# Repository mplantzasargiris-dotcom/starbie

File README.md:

# Starbie - Motion-Controlled Digital Pet

Starbie is a custom macropad PCB I designed for Half-lifes week 1.

I built this project to learn how to design a complete PCB, route connections, and place components properly in KiCad.

## Features:

* Custom routed PCB layout designed from scratch
* Fits mechanical key switches
* Built-in USB-C interface for power and data
* Compact macropad design

## What it is and why I made it:
Starbie is a custom-designed motion-controlled digital pet, built to function like a desktop Tamagotchi. I created this project to learn end-to-end PCB design, from drawing custom schematics and routing traces in KiCad to laying out physical components on a unique star-shaped board.

## How it works:
The board integrates a microcontroller (XIAO-ESP32-C3) connected to push buttons, indicator LEDs, and headers, allowing it to process user inputs and run digital pet logic.

## Schematics & Design:
Here is the schematic showing how all the components and power lines are wired together:

## PCB Design:

Everything was designed and routed in KiCad, focusing on clean trace routing and proper component layout for safe soldering and operation.

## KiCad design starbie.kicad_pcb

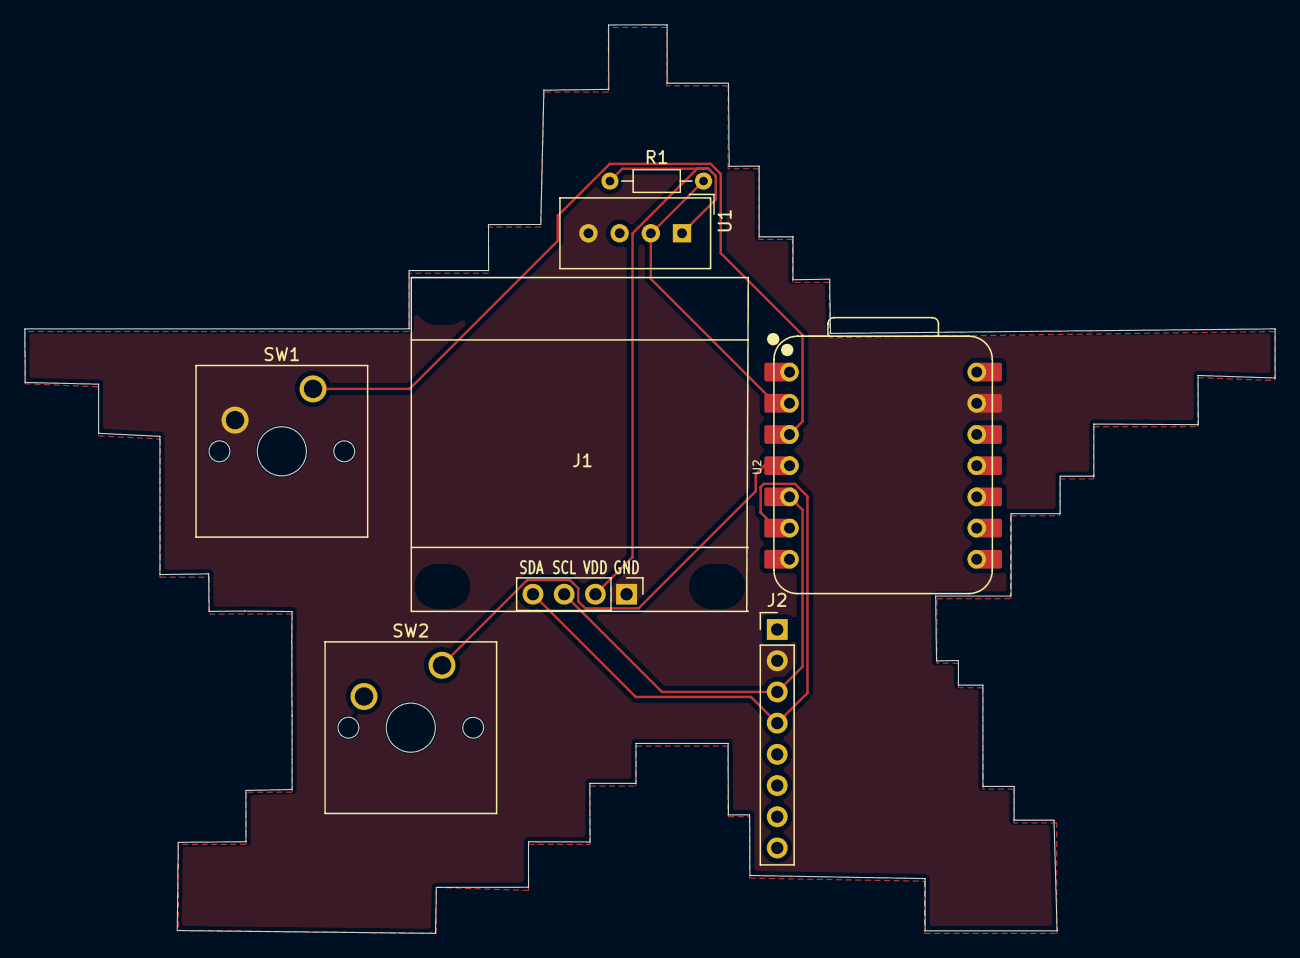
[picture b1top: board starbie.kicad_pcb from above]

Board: 2 copper layers, 101.8 x 74.0 mm, 7 parts (0 on the bottom side), 7 nets.

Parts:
J1: Conn_01x04_Pin; Display_128x64_096_I2C
J2: Conn_01x08_Pin; PinHeader_1x08_P2.54mm_Vertical
R1: 10k; R_Axial_DIN0204_L3.6mm_D1.6mm_P7.62mm_Horizontal
SW1, SW2: SW_Push; SW_Cherry_MX_1.00u_PCB
U1: DHT11; Aosong_DHT11_5.5x12.0_P2.54mm
U2: XIAO-ESP32-C3-SMD; XIAO-ESP32-C6-DIP

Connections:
+3.3V: J1.2, J2.1, R1.1, U1.1 (VDD), U2.12 (3V3_OUT)
/DHT11 DATA: R1.2, U1.2 (DATA), U2.2 (D1)
/GPIO2: SW1.1, U2.3 (D2)
/GPIO3: SW2.1 (1_1), U2.4 (D3)
/SCL: J1.3, J2.3, U2.5 (D4)
/SDA: J1.4, J2.4, U2.6 (D5)
GND: J1.1, J2.2, SW1.2, U1.4 (GND), U2.13 (GND)

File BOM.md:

# Starbie – bill of materials

<!-- Generated by Half Life from project cmuv88o5d0es601sm51l4azof. Edits here are overwritten on the next sync. -->
<!-- Generated: 2026-10-11T20:15:29.390Z -->

> [!NOTE]
> This parts list is mirrored from [Half Life](https://halflife.hackclub.com). Editing it here will not change the platform's copy, and the next sync overwrites this file.

| Week | Tier | Parts funding |
| --- | --- | --- |
| Week 1 | Tier 1 | $30.00 |

| Part | What it's for | Qty | Unit | Total | Vendor |
| --- | --- | --- | --- | --- | --- |
| [Conn_01x04_Pin](https://www.aliexpress.com/item/1005007093958549.html?spm=a2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 | Female header for expansions/l2C connections | 1 | $2.72 | $2.72 | [AliExpress](https://www.aliexpress.com/item/1005007093958549.html?spm=a2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 |
| [Conn_01x08_Pin](https://www.aliexpress.com/item/1005007093958549.html?spm=a2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 | 8-pin header for breakout connections or pin access. | 1 | $2.86 | $2.86 | [AliExpress](https://www.aliexpress.com/item/1005007093958549.html?spm=a2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 |
| [10k](https://www.aliexpress.com/item/1005010536514052.html?spm=a2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 | Pull-up resistor for button or data signal lines. | 1 | $0.78 | $0.78 | [AliExpress](https://www.aliexpress.com/item/1005010536514052.html?spm=a2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 |
| [SW_Push](https://www.aliexpress.com/item/32873398324.html?spm=a2g0o.c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 | buttons | 1 | $2.98 | $2.98 | [AliExpress](https://www.aliexpress.com/item/32873398324.html?spm=a2g0o.c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 |
| [DHT11](https://www.aliexpress.com/item/1005008953430940.html?spm=a2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 | Environment sensor | 1 | $1.99 | $1.99 | [AliExpress](https://www.aliexpress.com/item/1005008953430940.html?spm=a2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 |
| [XIAO-ESP32-C3-SMD](https://www.aliexpress.com/item/1005010085432476.html?spm=a2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 | Main microcontroller | 1 | $10.31 | $10.31 | [AliExpress](https://www.aliexpress.com/item/1005010085432476.html?spm=a2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 |
| **Parts subtotal** | — | — | — | **$21.64** | — |
| **Tax & shipping** | — | — | — | **$0.00** | — |
| **Total** | — | — | — | **$21.64** | — |

$8.36 left of the tier's funding.
